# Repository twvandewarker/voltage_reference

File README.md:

# voltage_reference

If you want to see the EAGLE files, you'll probably need my parts library, located here: https://github.com/twvandewarker/eagle_library

Quick voltage standard based on MAX6341. Trimmable 4.096V output accurate within 1mV and divided to 1.9V and 190mV, precision resistors from 1.96ohm to 10Mohm, and current standards from 190uA to 14mA. It can be powered with a 12-24V wall wart or by batteries with a normal barrel jack. A 9V is pushing it, since the protection Schottky drops 0.4V, the LDO drops 0.5V, and the minimum input voltage of the MAX chip is 8V. The LDO's max input voltage is 26V.

The BOM for the parts I used is included, and the zip file is the one I sent to the fab house. I used JLCPCB.

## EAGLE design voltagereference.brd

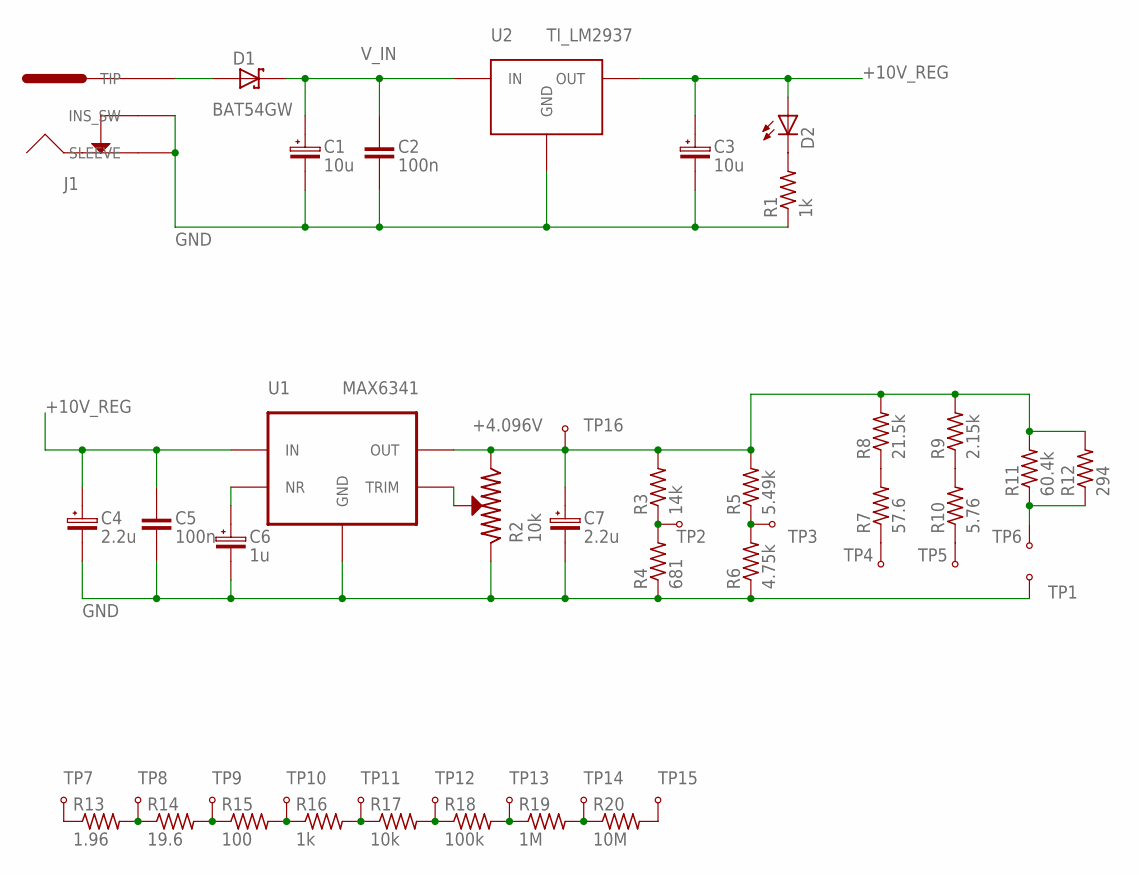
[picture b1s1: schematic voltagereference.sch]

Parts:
C1, C3: 10u; PANASONIC_EEE_4MM
C2, C5: 100n; 0805
C4, C7: 2.2u; PANASONIC_EEE_4MM
C6: 1u; PANASONIC_EEE_4MM
D1: BAT54GW; SOD123_NEX
D2: LED_0805; 0805_POL
J1: KOBICONN_163-179PH-EX
R1, R16: 1k; 0805
R2: 10k; BOURNS_3224X
R3: 14k; 0805
R4: 681; 0805
R5: 5.49k; 0805
R6: 4.75k; 0805
R7: 57.6; 0805
R8: 21.5k; 0805
R9: 2.15k; 0805
R10: 5.76; 0805
R11: 60.4k; 0805
R12: 294; 0805
R13: 1.96; 0603
R14: 19.6; 0603
R15: 100; 0805
R17: 10k; 0805
R18: 100k; 0805
R19: 1M; 0805
R20: 10M; 0805
TP1, TP2, TP3, TP4, TP5, TP6, TP7, TP8, TP9, TP10, TP11, TP12, TP13, TP14, TP15, TP16: KEYSTONE_500X
U1: MAX6341; SO8_MAX
U2: TI_LM2937; SOT223_TI

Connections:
0.19MA: R7.P$1 (1), TP4.P$1
1.9MA: R10.P$1 (1), TP5.P$1
14MA: R11.P$1 (1), R12.P$1 (1), TP6.P$1
+0.19V: R3.P$1 (1), R4.P$2 (2), TP2.P$1
+1.9V: R5.P$1 (1), R6.P$2 (2), TP3.P$1
+4.096V: C7.P$1 (1), R2.P$1 (1), R3.P$2 (2), R5.P$2 (2), R8.P$2 (2), R9.P$2 (2), R11.P$2 (2), R12.P$2 (2), TP16.P$1, U1.P$6 (OUT)
+10V_REG: C3.P$1 (1), C4.P$1 (1), C5.P$1 (1), D2.P$1 (A), U1.P$2 (IN), U2.P$3 (OUT)
GND: C1.P$2 (2), C2.P$2 (2), C3.P$2 (2), C4.P$2 (2), C5.P$2 (2), C6.P$2 (2), C7.P$2 (2), J1.P$2 (SLEEVE), J1.P$3 (INS_SW), J1.P$5 (SLEEVE), J1.P$6 (INS_SW), R1.P$1 (1), R2.P$3 (3), R4.P$1 (1), R6.P$1 (1), TP1.P$1, U1.P$4 (GND), U2.P$2 (GND), U2.P$4 (GND)
unnamed: D2.P$2 (C), R1.P$2 (2)
unnamed: R7.P$2 (2), R8.P$1 (1)
unnamed: R9.P$1 (1), R10.P$2 (2)
unnamed: R13.P$2 (2), R14.P$1 (1), TP8.P$1
unnamed: R14.P$2 (2), R15.P$1 (1), TP9.P$1
unnamed: R15.P$2 (2), R16.P$1 (1), TP10.P$1
unnamed: R16.P$2 (2), R17.P$1 (1), TP11.P$1
unnamed: R17.P$2 (2), R18.P$1 (1), TP12.P$1
unnamed: R18.P$2 (2), R19.P$1 (1), TP13.P$1
unnamed: R19.P$2 (2), R20.P$1 (1), TP14.P$1
unnamed: R13.P$1 (1), TP7.P$1
unnamed: R20.P$2 (2), TP15.P$1
NR: C6.P$1 (1), U1.P$3 (NR)
TIP: D1.P$1 (A), J1.P$1 (TIP), J1.P$4 (TIP)
TRIM: R2.P$2 (2), U1.P$5 (TRIM)
V_IN: C1.P$1 (1), C2.P$1 (1), D1.P$2 (C), U2.P$1 (IN)

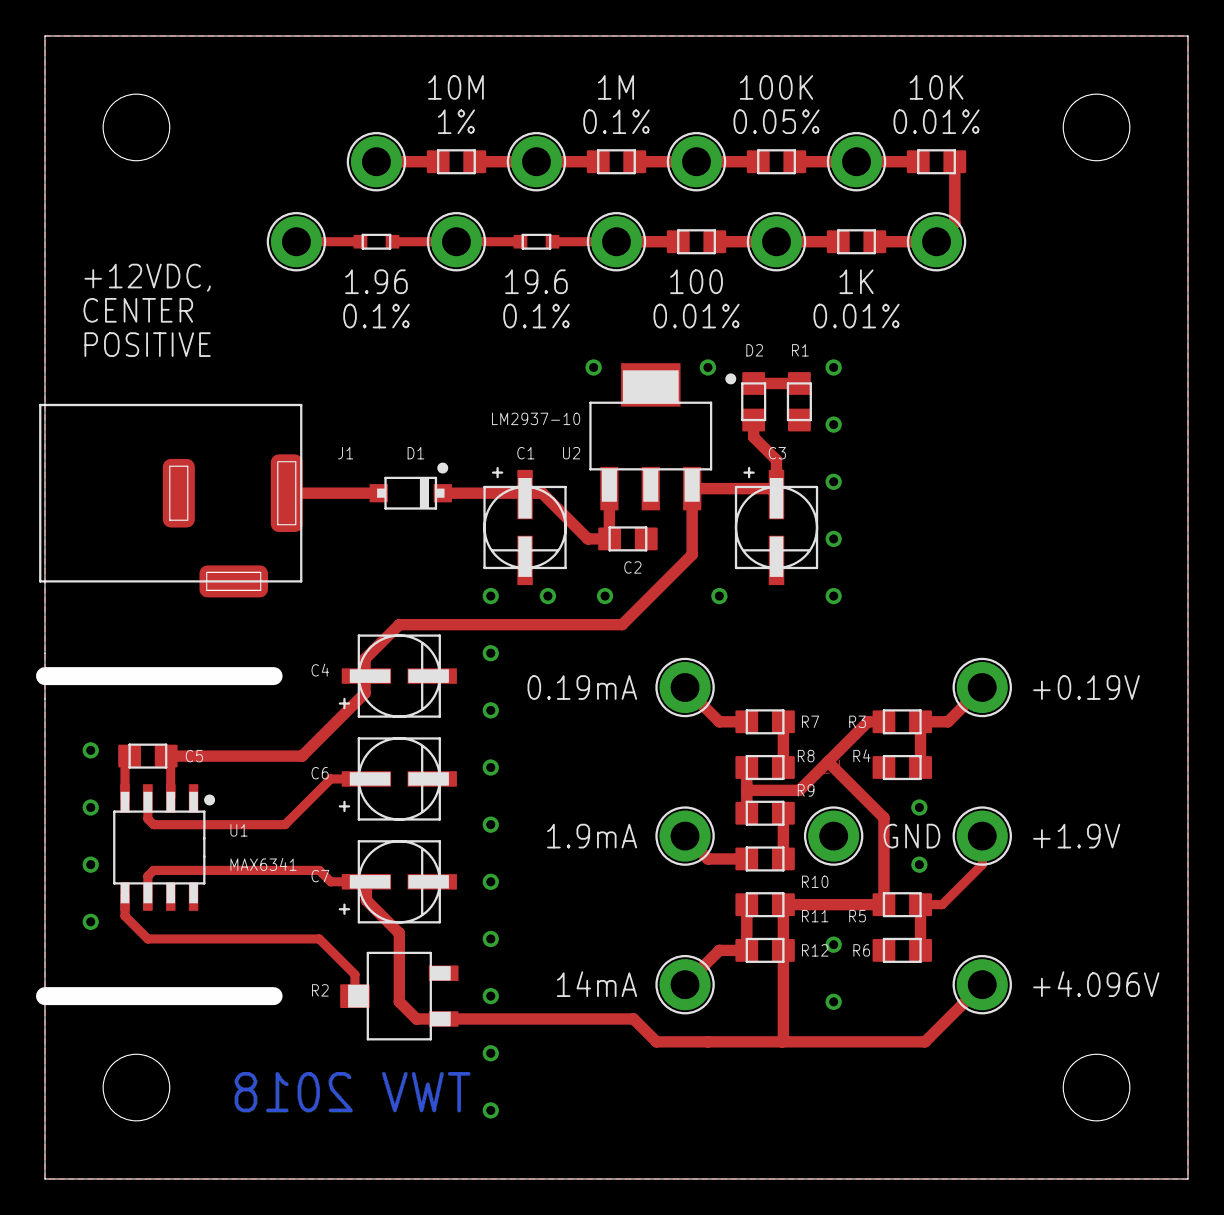
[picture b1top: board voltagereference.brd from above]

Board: 2 copper layers, 63.0 x 62.5 mm, 48 parts (0 on the bottom side), 24 nets.

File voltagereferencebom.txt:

Partlist exported from /home/twv/EAGLE/projects/VoltageReference/voltagereference.sch at 8/15/18 10:03 PM

Part Value                 Device                Package               Description 
C1   10u                   PANASONIC_EEE_4MM     PANASONIC_EEE_4MM                 
C2   100n                  C_0805                0805                              
C3   10u                   PANASONIC_EEE_4MM     PANASONIC_EEE_4MM                 
C4   2.2u                  PANASONIC_EEE_4MM     PANASONIC_EEE_4MM                 
C5   100n                  C_0805                0805                              
C6   1u                    PANASONIC_EEE_4MM     PANASONIC_EEE_4MM                 
C7   2.2u                  PANASONIC_EEE_4MM     PANASONIC_EEE_4MM                 
D1   NEX_BAT54GW           NEX_BAT54GW           SOD123_NEX                        
D2   LED_0805              LED_0805              0805_POL                          
J1   KOBICONN_163-179PH-EX KOBICONN_163-179PH-EX KOBICONN_163-179PH-EX             
R1   1k                    R_0805                0805                              
R2   10k                   BOURNS_3224X          BOURNS_3224X                      
R3   14k                   R_0805                0805                              
R4   681                   R_0805                0805                              
R5   5.49k                 R_0805                0805                              
R6   4.75k                 R_0805                0805                              
R7   57.6                  R_0805                0805                              
R8   21.5k                 R_0805                0805                              
R9   2.15k                 R_0805                0805                              
R10  5.76                  R_0805                0805                              
R11  60.4k                 R_0805                0805                              
R12  294                   R_0805                0805                              
R13  1.96                  R_0603                0603                              
R14  19.6                  R_0603                0603                              
R15  100                   R_0805                0805                              
R16  1k                    R_0805                0805                              
R17  10k                   R_0805                0805                              
R18  100k                  R_0805                0805                              
R19  1M                    R_0805                0805                              
R20  10M                   R_0805                0805                              
TP1  KEYSTONE_500X         KEYSTONE_500X         KEYSTONE_500X                     
TP2  KEYSTONE_500X         KEYSTONE_500X         KEYSTONE_500X                     
TP3  KEYSTONE_500X         KEYSTONE_500X         KEYSTONE_500X                     
TP4  KEYSTONE_500X         KEYSTONE_500X         KEYSTONE_500X                     
TP5  KEYSTONE_500X         KEYSTONE_500X         KEYSTONE_500X                     
TP6  KEYSTONE_500X         KEYSTONE_500X         KEYSTONE_500X                     
TP7  KEYSTONE_500X         KEYSTONE_500X         KEYSTONE_500X                     
TP8  KEYSTONE_500X         KEYSTONE_500X         KEYSTONE_500X                     
TP9  KEYSTONE_500X         KEYSTONE_500X         KEYSTONE_500X                     
TP10 KEYSTONE_500X         KEYSTONE_500X         KEYSTONE_500X                     
TP11 KEYSTONE_500X         KEYSTONE_500X         KEYSTONE_500X                     
TP12 KEYSTONE_500X         KEYSTONE_500X         KEYSTONE_500X                     
TP13 KEYSTONE_500X         KEYSTONE_500X         KEYSTONE_500X                     
TP14 KEYSTONE_500X         KEYSTONE_500X         KEYSTONE_500X                     
TP15 KEYSTONE_500X         KEYSTONE_500X         KEYSTONE_500X                     
TP16 KEYSTONE_500X         KEYSTONE_500X         KEYSTONE_500X                     
U1   MAX6341               MAXIM_MAX6341         SO8_MAX                           
U2   TI_LM2937             TI_LM2937             SOT223_TI

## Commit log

2018-12-26 Added pdfs, modified schematic
